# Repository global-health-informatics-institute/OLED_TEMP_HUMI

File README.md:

# OLED_TEMP_HUMI
This is a sample code for OLED and DHT11 Sensor to red Temperature and Humidity and Display on OLED.

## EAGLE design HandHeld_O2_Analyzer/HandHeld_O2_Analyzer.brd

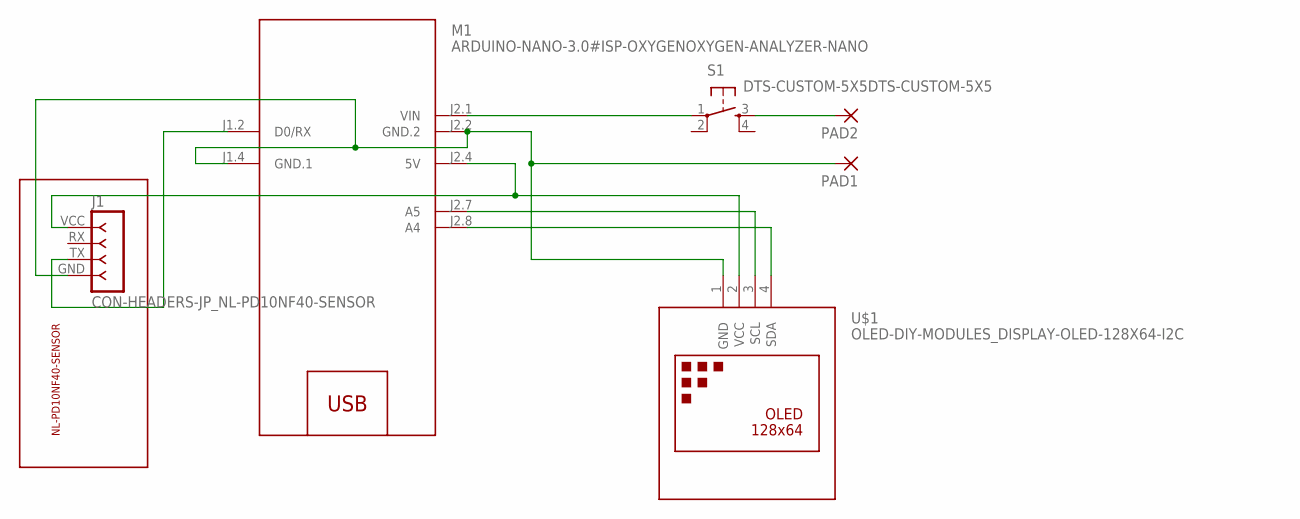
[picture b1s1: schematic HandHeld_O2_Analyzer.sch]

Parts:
J1: CON-HEADERS-JP_NL-PD10NF40-SENSOR
M1: ARDUINO-NANO-3.0#ISP-OXYGENOXYGEN-ANALYZER-NANO; ARDUINO-NANO-3.0#ISP-OXYGEN
PAD1, PAD2: WIREPAD_2,54/0,8
S1: DTS-CUSTOM-5X5DTS-CUSTOM-5X5; DTS-CUSTOM-5X5
U$1: OLED-DIY-MODULES_DISPLAY-OLED-128X64-I2C

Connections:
unnamed: M1.J2.8 (A4), U$1.4 (SDA)
unnamed: M1.J2.7 (A5), U$1.3 (SCL)
unnamed: J1.GND, M1.J1.4 (GND.1), M1.J2.2 (GND.2), PAD1.1, U$1.1 (GND)
unnamed: J1.VCC, M1.J2.4 (5V), U$1.2 (VCC)
unnamed: M1.J2.1 (VIN), S1.1
unnamed: PAD2.1, S1.3
unnamed: J1.TX, M1.J1.2 (D0/RX)

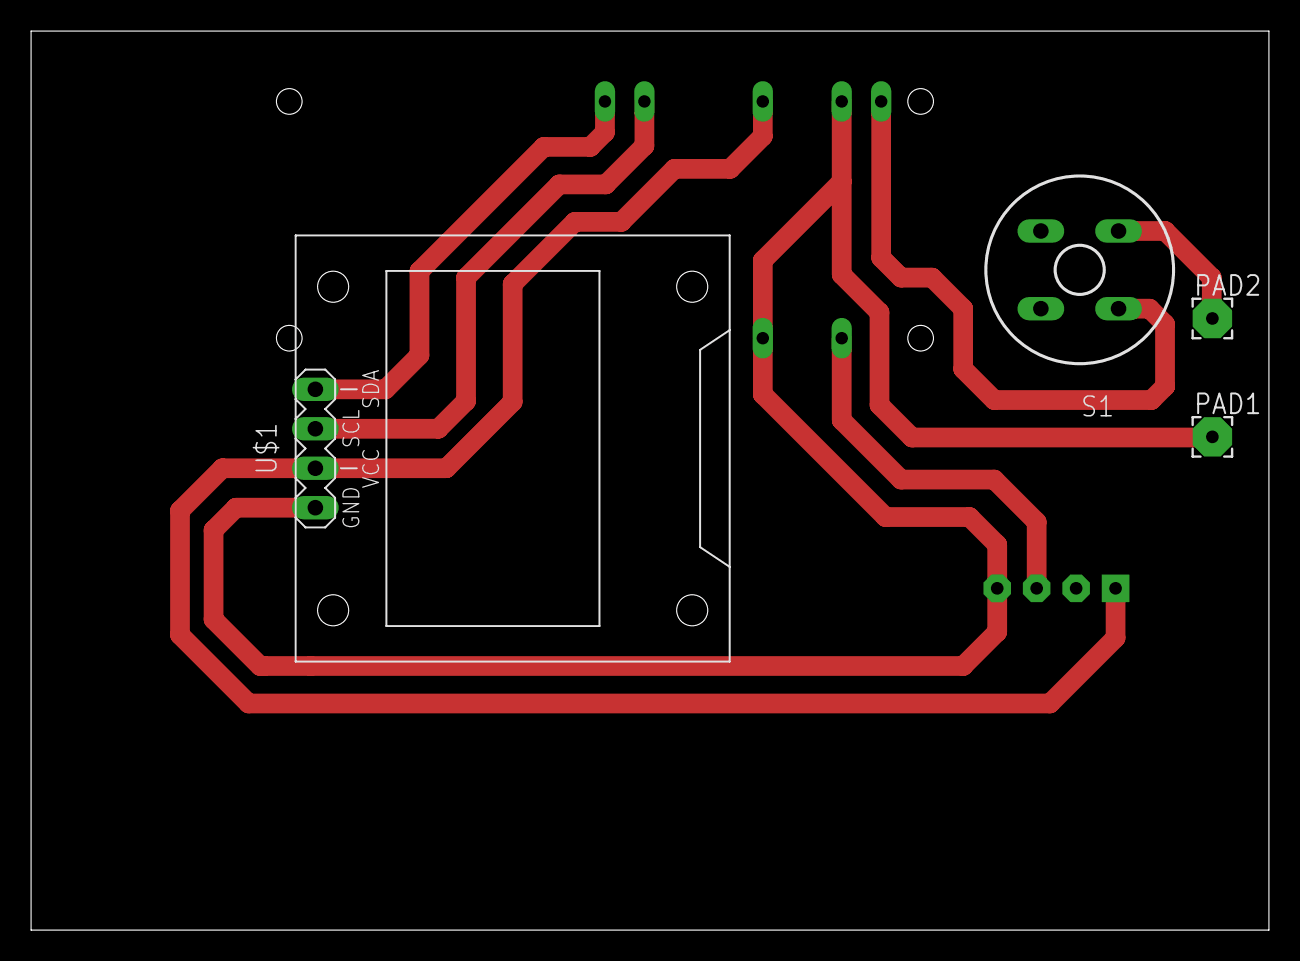
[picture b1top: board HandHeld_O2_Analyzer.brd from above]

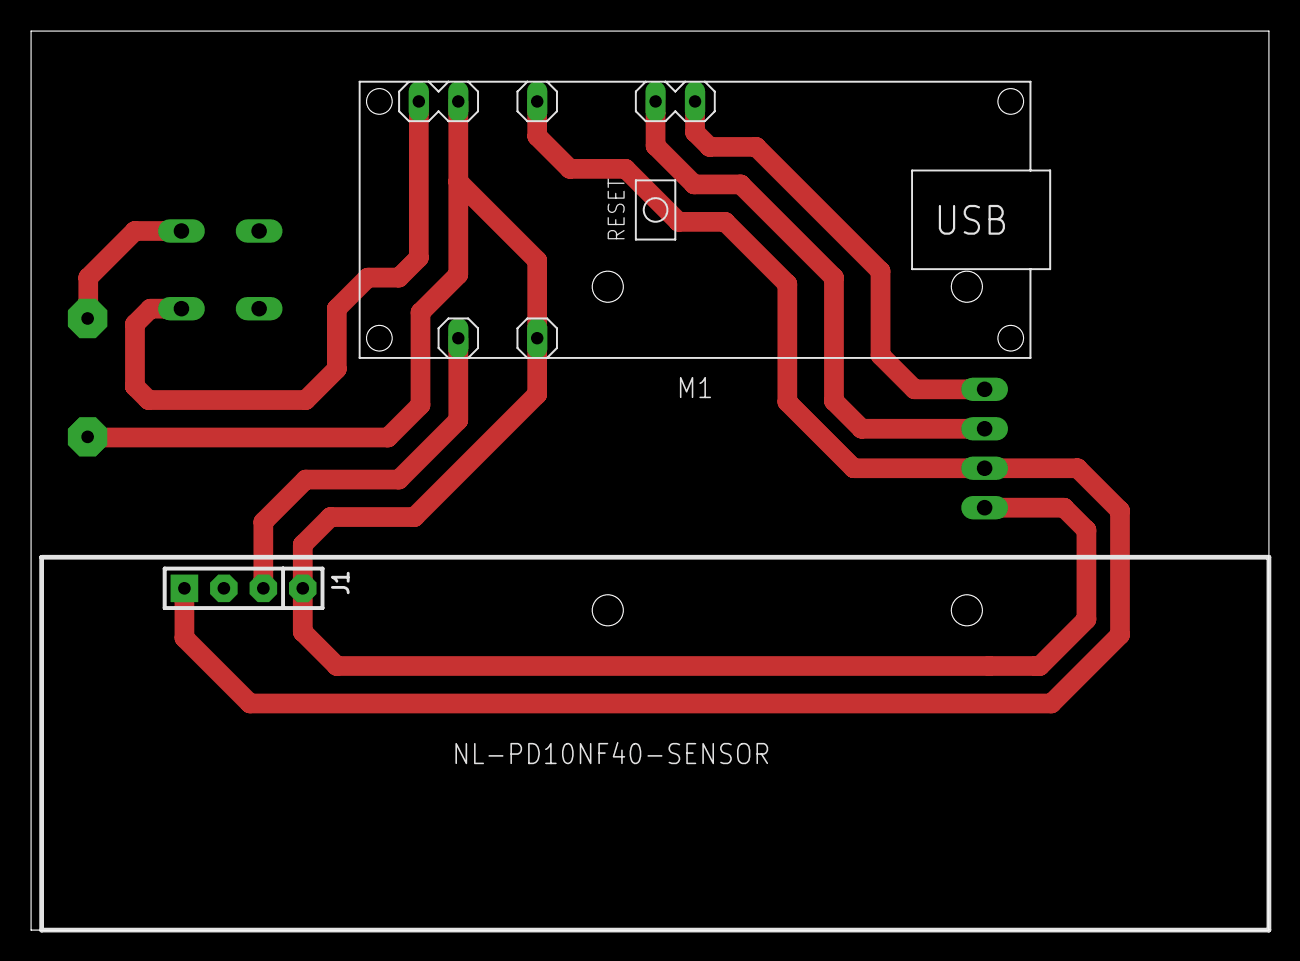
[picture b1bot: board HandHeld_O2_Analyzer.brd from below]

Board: 2 copper layers, 79.7 x 57.9 mm, 6 parts (2 on the bottom side), 7 nets.

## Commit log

2021-02-20 OLED and DHT11
2021-03-01 The Eagle file for Analyzer

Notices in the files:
parts and their libraries:
GHIdiy-modules: Released under the Creative Commons Attribution 4.0 International License: http://creativecommons.org/licenses/by/4.0
